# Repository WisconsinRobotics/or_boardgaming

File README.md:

# or_boardgaming
Code for Outreach's Board Game Playing Robot

Integrated logic:
- turn on camera
- setup
    - run the corner detect logic and get the board params
    - detect the lines and points of board n create the perspective transform as needed

- when human turn:
    - wait until button pressed
- when bot turn:
    - determine current board state
        - click pic
        - find current piece positions
        - update board state
    - get best move
        - run tic tac toe algorithm to determine next best position
    - get path
        - determine location of best move from board position
        - smooth interp to go from rest location to pieces location to best move location to rest location
    - actual move
        - execute path to reach pieces
        - pick up piece
        - execute said path place piece
        - move arm to rest position away from human
    - indicate end of turn with light n sound

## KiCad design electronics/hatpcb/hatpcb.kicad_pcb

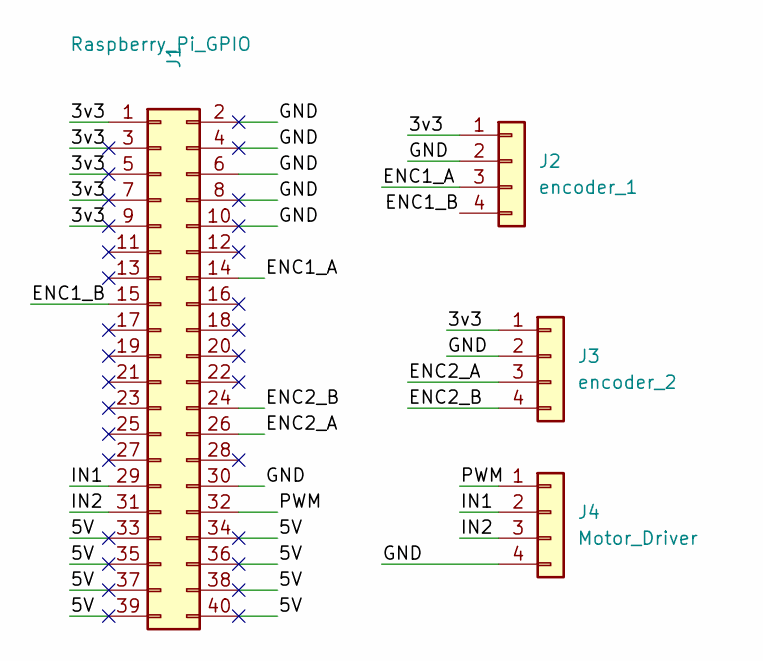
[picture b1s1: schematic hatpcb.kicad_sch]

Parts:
J1: Raspberry_Pi_GPIO; PinHeader_2x20_P2.54mm_Vertical
J2: encoder_1; PinHeader_1x04_P2.54mm_Vertical
J3: encoder_2; PinHeader_1x04_P2.54mm_Vertical
J4: Motor_Driver; PinHeader_1x04_P2.54mm_Vertical

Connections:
/3v3: J1.1, J1.3, J1.5, J1.7, J1.9, J2.1, J3.1
/5V: J1.33, J1.34, J1.35, J1.36, J1.37, J1.38, J1.39, J1.40
/ENC1_A: J1.14, J2.3
/ENC1_B: J1.15, J2.4
/ENC2_A: J1.26, J3.3
/ENC2_B: J1.24, J3.4
/GND: J1.2, J1.4, J1.6, J1.8, J1.10, J1.30, J2.2, J3.2, J4.4
/IN1: J1.29, J4.2
/IN2: J1.31, J4.3
/PWM: J1.32, J4.1

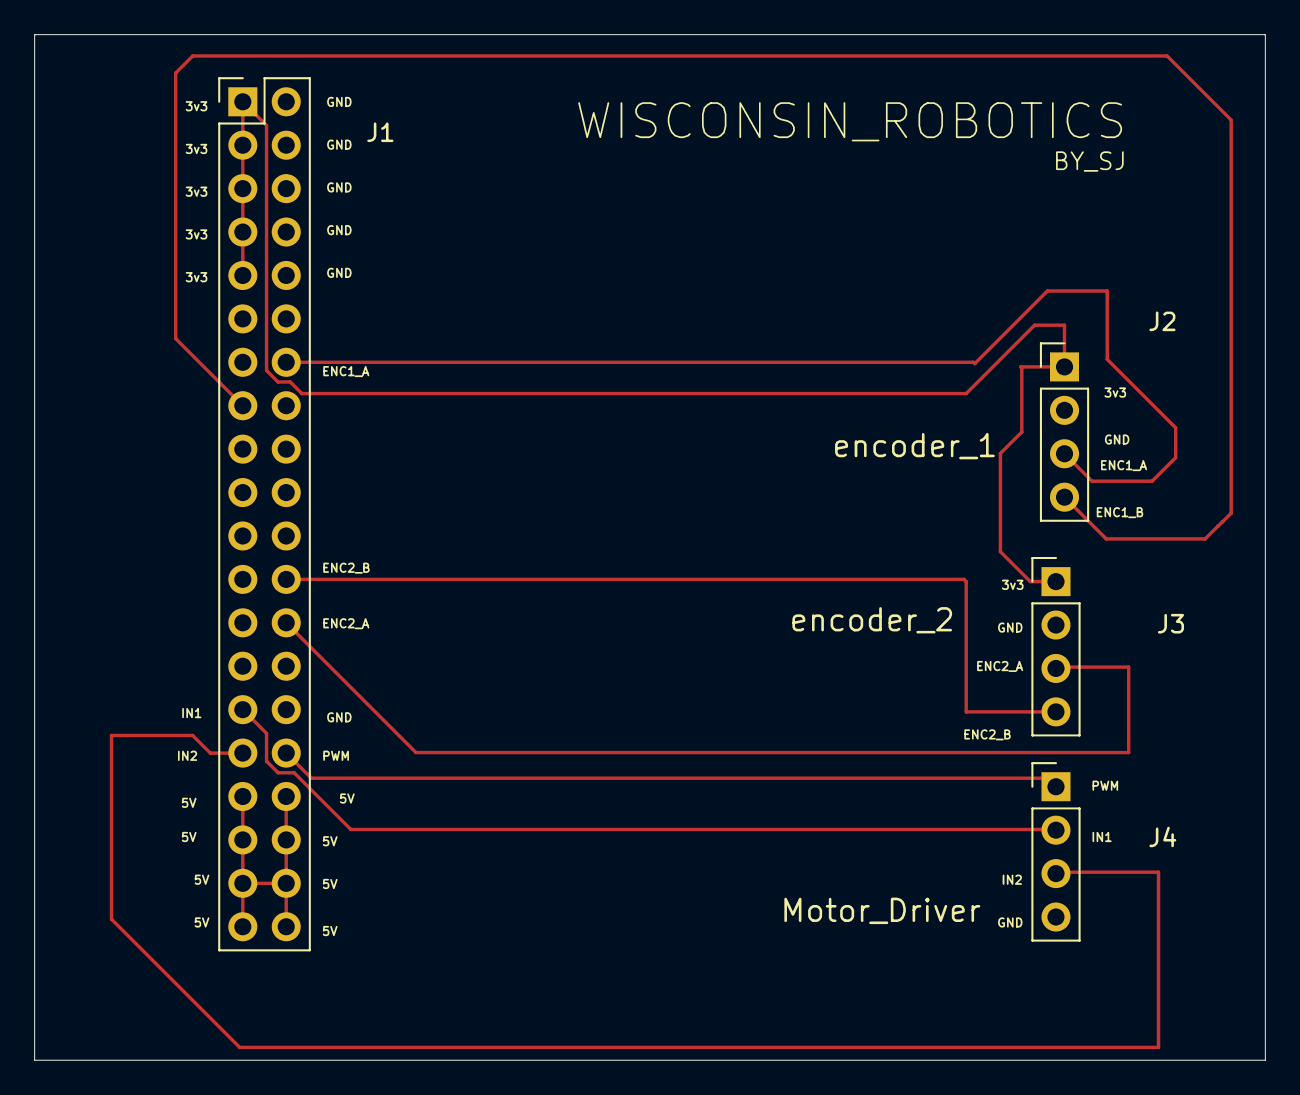
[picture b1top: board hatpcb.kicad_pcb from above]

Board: 2 copper layers, 72.0 x 60.0 mm, 4 parts (0 on the bottom side), 10 nets.

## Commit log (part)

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2024-10-04 added opencv code that detects contours + corners
2024-10-28 preliminary robot controls, probably doesn't work
2024-10-29 read encoder value
2024-10-29 working reading encoders code
2024-11-19 functional closed-loop control!
2024-12-04 finished tic tac toe algo v1
2024-12-11 Add files via upload
    Real time analysis of game board that detects the orange color of the pieces. Left to implement: Saving or somehow indicating position of pieces on the board.
2025-03-27 integration start
2025-03-27 moving tic tac toe logic into its own file
2025-03-27 moving files
2025-03-31 moved dual_max folder
2025-04-01 created new files
2025-04-09 adding tic tac toe logic with numpy
2025-04-09 cleaner code
2025-04-09 speghetti moment
2025-04-09 made naming better
2025-04-10 Intialized motors in gameplay.py, Made logic for move_xy in path_planning.py
2025-04-10 encoder test
2025-04-10 motors kinda not really but trust
2025-04-10 we love hypothetical async
2025-04-10 updated file structure and uncommented hardware inits
2025-04-11 Added blue detection cv_functions.py
2025-04-11 Add test pics using actual board and pictures
2025-04-11 stuff for path planning:
2025-04-11 initialized z-motor
2025-11-25 motor testing
2025-12-02 changes on pi
2025-12-09 PCB files
2026-02-16 Add hatpcb KiCad project
2026-02-21 Update hatpcb routing
2026-03-13 gantry working
2026-03-13 uv setup
2026-03-13 removed comment
2026-03-17 cleaned up gantry.py
2026-03-17 added .gitignore
2026-04-13 who knows
2026-04-13 deleted stupid folder
2026-04-13 made claw move smoother
2026-04-13 added camera.py
2026-04-17 who knows v2
